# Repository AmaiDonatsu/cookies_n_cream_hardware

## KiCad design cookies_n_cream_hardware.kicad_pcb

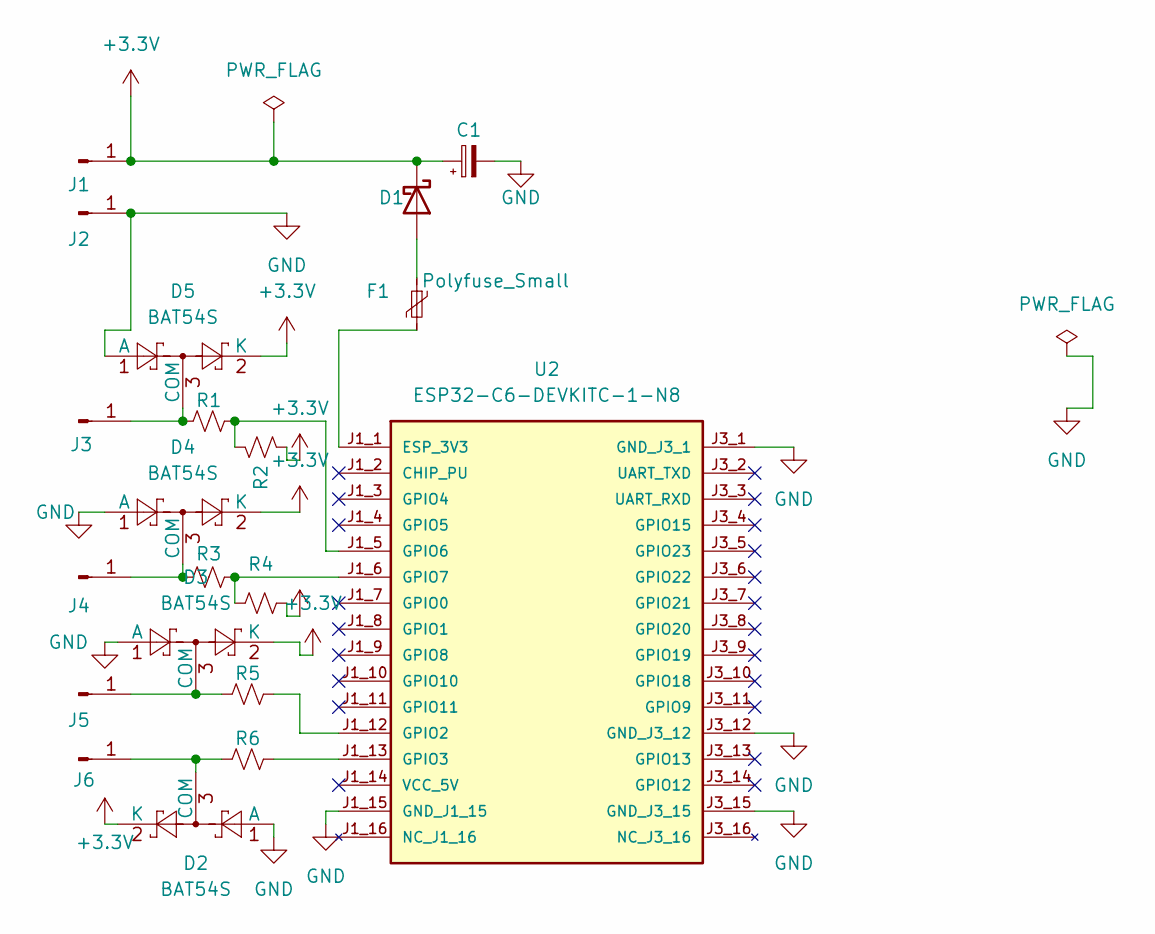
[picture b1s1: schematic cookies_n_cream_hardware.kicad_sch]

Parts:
C1: C_Polarized_Small; CP_Radial_D5.0mm_P2.00mm
D1: D_Schottky; D_DO-41_SOD81_P7.62mm_Horizontal
D2, D3, D4, D5: BAT54S; SOT-23
F1: Polyfuse_Small; Fuse_BelFuse_0ZRE0012FF_L8.3mm_W3.8mm
J1, J2, J3, J4, J5, J6: Conn_01x01_Pin; PinHeader_1x01_P2.54mm_Vertical
R1, R2, R3, R4, R5, R6: R_Small_US; R_Axial_DIN0207_L6.3mm_D2.5mm_P7.62mm_Horizontal
U2: ESP32-C6-DEVKITC-1-N8; MODULE_ESP32-C6-DEVKITC-1-N8; PARTREV 1.3

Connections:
+3.3V: C1.1, D1.1 (K), D2.2 (K), D3.2 (K), D4.2 (K), D5.2 (K), J1.1 (Pin_1_1), R2.1, R4.1
GND: C1.2, D2.1 (A), D3.1 (A), D4.1 (A), D5.1 (A), J2.1 (Pin_1_1), U2.J1_15 (GND_J1_15), U2.J3_1 (GND_J3_1), U2.J3_12 (GND_J3_12), U2.J3_15 (GND_J3_15)
unnamed: D1.2 (A), F1.1
unnamed: D2.3 (COM), J6.1 (Pin_1_1), R6.1
unnamed: D3.3 (COM), J5.1 (Pin_1_1), R5.1
unnamed: D4.3 (COM), J4.1 (Pin_1_1), R3.2
unnamed: D5.3 (COM), J3.1 (Pin_1_1), R1.2
unnamed: F1.2, U2.J1_1 (ESP_3V3)
unnamed: R5.2, U2.J1_12 (GPIO2)
unnamed: R6.2, U2.J1_13 (GPIO3)
unnamed: R1.1, R2.2, U2.J1_5 (GPIO6)
unnamed: R3.1, R4.2, U2.J1_6 (GPIO7)

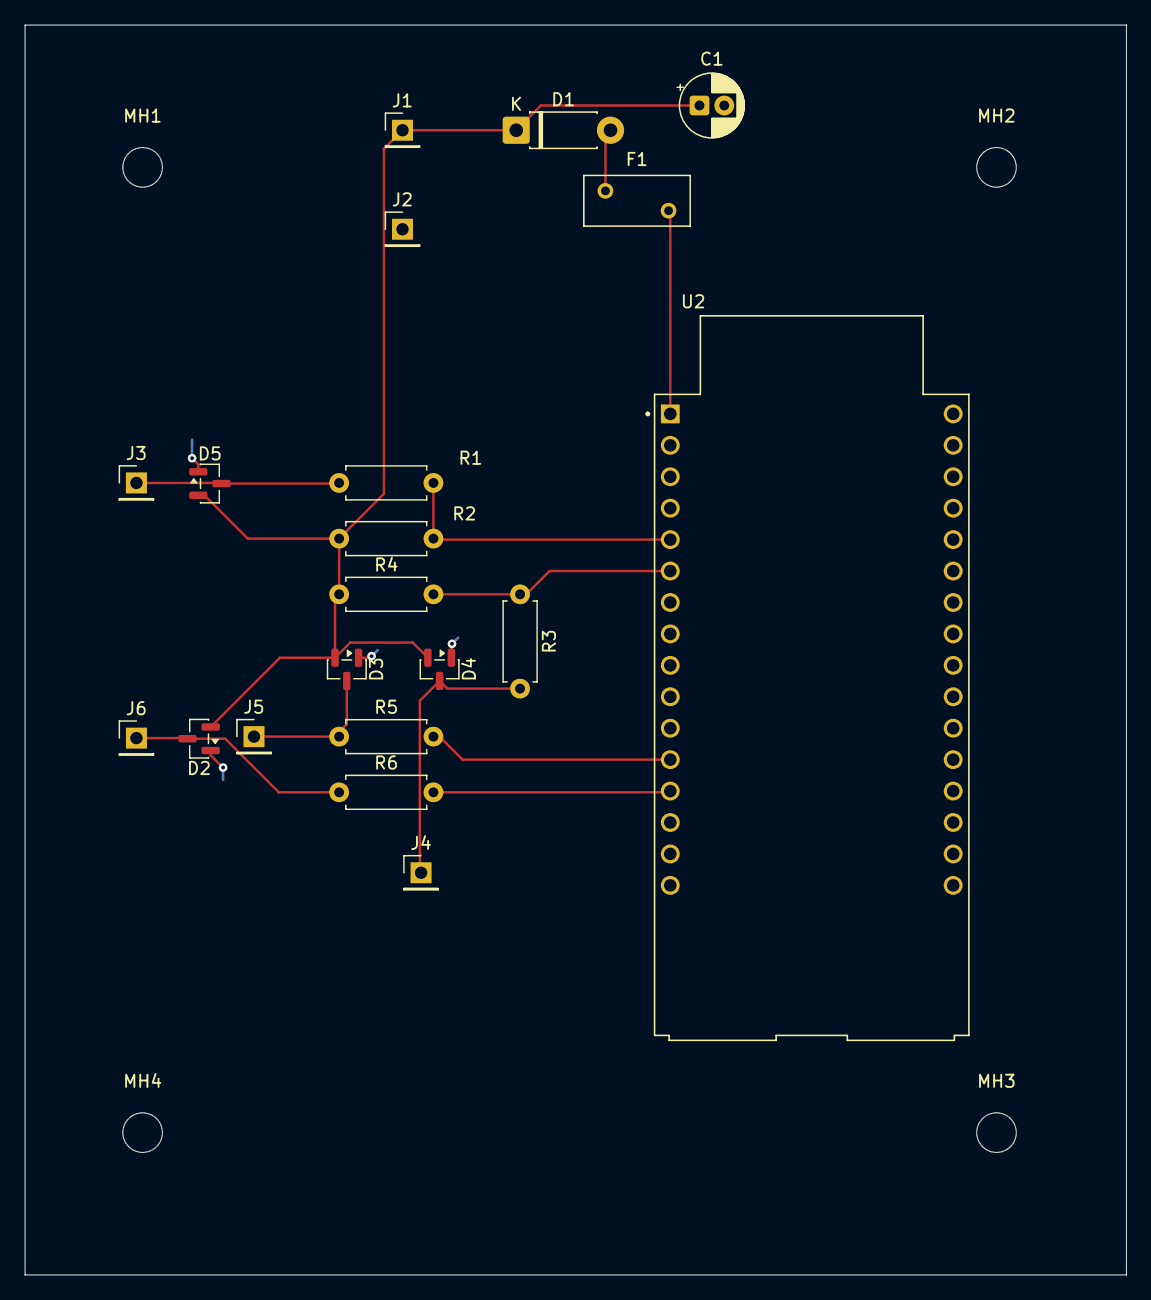
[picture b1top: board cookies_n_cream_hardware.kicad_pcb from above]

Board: 2 copper layers, 89.0 x 101.0 mm, 24 parts (0 on the bottom side), 12 nets.

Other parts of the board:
MH1, MH2, MH3, MH4: MountingHole_3.2mm_M3
